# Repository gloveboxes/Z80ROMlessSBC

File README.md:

# Z80 ROMless SBC

This repository contains a work-in-progress engineering specification and
reference implementation for a ROMless Z80 computer supervised by a Raspberry
Pi Pico 2 W. The design has not yet been physically built or qualified; treat
all electrical and timing claims as proposed until the staged bench tests pass.

## Clone the project

```sh
git clone --recurse-submodules https://github.com/gloveboxes/Z80ROMlessSBC.git
```

On Windows, enable Developer Mode and run `git config --global core.symlinks true`
before cloning. Then open the `Z80ROMlessSBC` directory in a terminal or VS Code.

## Documentation

- [Browse the MkDocs source](docs/docs/en/index.md)
- [Read the published documentation](https://gloveboxes.github.io/Z80ROMlessSBC/)
- [Follow the staged breadboard implementation plan](docs/docs/en/implementation/index.md)
- [Review the KiCad schematic](hardware/kicad/exports/z80_romless_sbc.pdf)
- [Choose a PCB: DIP or partial-SMT](docs/docs/en/pcb/variants.md)

The documentation covers the component inventory, pin maps, voltage domains,
breadboard construction, Z80-assisted loading, firmware architecture, CP/M storage,
DHO814/DSLogic Plus measurements, and the complete phase-by-phase bring-up
procedure.

Phases 0-10 build the three-BB830 breadboard prototype. Two four-layer PCBs
implement the same assisted-loader circuit: an **85 x 96 mm DIP / through-hole
board** for hand assembly, and a **98.3 x 60 mm partial-SMT board** for JLCPCB
assembly. DIP is the budget-oriented option for one hand-built machine;
partial-SMT reduces hand-soldering and uses a different SRAM part.
Each PCB's 20 MHz target requires separate qualification. All builds use
fixed HCT32 logic and Z80-executed RAM loading, with no PLD programmer or
address expander.

## Related projects

Build C applications, package CP/M disks, and run them on this Z80 computer.
The supplied disks already include a default set of applications.

<table>
  <tr>
    <td width="50%" valign="top">
      <a href="https://davidly.github.io/dcc/">
        <br />
        <strong>DCC C Compiler</strong>
      </a>
      <p>Build Z80 CP/M applications on Windows, macOS, or Linux. C89 with selected C99/C11 features.</p>
      <a href="https://davidly.github.io/dcc/">Explore DCC ↗</a>
    </td>
    <td width="50%" valign="top">
      <a href="https://gloveboxes.github.io/Altair-8800-AI-Edition/">
        <br />
        <strong>Altair 8800 AI Edition</strong>
      </a>
      <p>Explore CP/M applications and build Altair disk images for deployment to this project's Pico flash storage.</p>
      <a href="https://gloveboxes.github.io/Altair-8800-AI-Edition/">Explore Altair ↗</a>
    </td>
  </tr>
</table>

See the [application and disk workflow](https://gloveboxes.github.io/Z80ROMlessSBC/related-projects/)
when you reach Phases 9–10, after completing the earlier hardware bring-up tests.

## Build

Configure and build the Pico firmware and CP/M artifacts from the repository
root:

```sh
cmake -S . -B build -G Ninja \
  -DPICO_BOARD=pico2_w
cmake --build build --target z80_cpm_images -j
```

In VS Code, open the repository folder and select **Terminal → Run Task** to
choose a build or build-and-flash task for your hardware's current phase. See
the [VS Code deployment options](docs/docs/en/system/firmware-build.md#vs-code-deployment-options)
and [toolchain setup](docs/docs/en/toolchain.md) for prerequisites and flash safety.

Phase 10 builds on the Phase 9 automatic loader.
Wi-Fi credentials and the remote-FS server address are provisioned over USB
with Ctrl-] n and stored in ENV, not compiled into firmware. The browser
terminal takes over CP/M while connected and returns it to USB on disconnect.

See [Firmware and CP/M build](docs/docs/en/system/firmware-build.md) for
prerequisites and provisioning, and [Building the documentation](docs/docs/en/development/building-docs.md)
for MkDocs and local preview commands.

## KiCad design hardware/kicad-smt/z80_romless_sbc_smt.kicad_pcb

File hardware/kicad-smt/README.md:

# Partial-SMT PCB (JLCPCB assembly variant)

This is a separate KiCad project for a 98.3 × 60 mm, four-layer board. JLCPCB
assembles every top-side SMT part, including the Raspberry Pi Pico 2 W module,
and only four parts are hand-soldered:

| Ref | Part | Assembly |
| --- | --- | --- |
| U1 | Z84C0020PEC, DIP-40 | Hand-soldered |
| A2 | 0.91 in SSD1315 OLED on a 1×4 2.54 mm female header, 5.0 mm body | Hand-soldered |
| J2 | Pico GPIO expansion header, 1×4 | Hand-soldered |
| J3 | Auxiliary external 5 V header, 1×2 | Hand-soldered |

All other parts are JLCPCB-assembled from the LCSC numbers in the schematic:

- SOIC logic and SOP-32 SRAM.
- 0603 resistors and capacitors.
- SS14 diode.
- SMT electrolytic capacitors.
- Power-only USB-C receptacle with 5.1 kΩ CC pull-downs.
- Raspberry Pi Pico 2 W (C42394205), reflowed on its castellated pads with
  KiCad's `RaspberryPi_Pico_W_SMD` footprint.

The bulk capacitors are C8-C10 = 22 µF, 35 V (LCSC C150379) and C11 = 100 µF,
16 V (LCSC C346929). Both parts use the same 6.3 × 5.4 mm case, so they look
the same size in JLCPCB's placement preview; check the BOM part numbers and
values rather than judging capacitance from the rendered body size.

## Sources

- `scripts/build-kicad-smt-schematic.py` generates the schematic, symbols and
  `reports/net_manifest.json`. Each component declares its assembly method,
  `jlc` or `hand`. JLC parts must carry an LCSC number.
- `scripts/build-kicad-smt-pcb.py` generates placement, rules, keepouts,
  labels and 3D models. `reports/z80_romless_sbc_smt.ses` holds the accepted
  Freerouting result.
- `scripts/export-jlc-assembly.py` writes the JLCPCB BOM and CPL from the
  manifest and the routed board.

## Build and validate

Save and close the project in KiCad, then run from the repository root:

```sh
PYTHON=.venv-kicad/bin/python npm run kicad:smt
```

The pipeline publishes `exports/`, `fabrication/` and `reports/` only after all
of these pass:

- ERC and netlist/manifest parity.
- PCB/DSN reproduction and zone-refilled DRC.
- Route-length budgets.
- The Gerber silk-to-mask audit (≥ 0.18 mm, target 0.20 mm).
- Every track ≥ 0.155 mm from any solder-mask opening it does not connect
  to. JLCDFM rates more than 0.15 mm as good.
- The JLC BOM/CPL consistency check.

It does not modify `hardware/kicad/`.

### JLCDFM design rules

- Solder-mask openings are 0.05 mm per side larger than the copper. J1's
  0.5 mm-pitch pads use 0.04 mm. JLCDFM flags 1:1 (zero-expansion) openings.
- J1's signal pads are trimmed 0.05 mm narrower than the stock footprint.
  This widens their copper gaps to 0.25 mm and leaves mask bridges of
  0.17 mm. JLCDFM rates bridges of 0.15 mm or more as good; the generator
  enforces 0.16 mm or a merged opening.
- After the routing session is imported, the generator straightens
  Freerouting's 45° pad exits. A run then cannot skim its own pad's mask
  opening.
- JLCDFM measures vias against rectangular pads as if the corners were
  square. A via sitting diagonally off a rounded SOIC corner therefore
  reports about 0.05 mm closer than it is. After import, the generator
  nudges each such via (and its track ends) until it is ≥ 0.16 mm from
  every square-cornered mask opening.
- The Pico footprint keeps the library's landing pads for the module's
  underside test points (TP1–TP6), SWD pads and USB shell legs. They are
  unconnected, and routed copper clears them. The library's
  "suggested RF board edge" keepouts are replaced by the enclosed antenna
  window and bridge keepout; the antenna keepout itself is retained.
- J1's stacked USB-C pad pairs (A1/B12, A4/B9, A9/B4, A12/B1) keep both
  copper pads but emit one mask and paste opening each.
- SMT pads sit at least 3.07 mm from other parts' through-hole pads.
  JLCDFM rates more than 3.05 mm as good. J2 and J3 sit 2.85 mm from the
  left edge so their pads clear the Pico castellations by 3.12 mm. J1's own shell legs are part of
  the same footprint, and JLCDFM does not report them.
- J1's plated shell slots are widened to 0.85 mm (1.9 mm and 1.75 mm long)
  with a 0.2 mm annular ring. Each slot is moved 0.125 mm outward so its
  inner edge stays at the stock position. JLCDFM rates slots wider than
  0.81 mm as good; the generator enforces 0.82 mm and at least 2:1.
  Dry-fit the purchased C393939 before ordering.

## Fabrication package

| File | Upload to |
| --- | --- |
| `fabrication/z80_romless_sbc_smt-gerbers.zip` | PCB order (Gerbers + PTH/NPTH drills) |
| `fabrication/assembly/z80_romless_sbc_smt-jlc-bom.csv` | PCBA "BOM file" |
| `fabrication/assembly/z80_romless_sbc_smt-jlc-cpl.csv` | PCBA "CPL file" |

The ZIP contains:

- Front, GND plane, +5 V plane and back copper.
- Front paste, used for the assembly stencil.
- Both solder masks and both silkscreens.
- The outline, including the enclosed Pico antenna window.
- The job file.
- Separate plated and non-plated millimetre Excellon drill files.

The full BOM (`z80_romless_sbc_smt-bom.csv`, including hand-soldered parts),
the KiCad position file, IPC-D-356 netlist, drill maps and report sit next to
the ZIP; they are not uploaded.

## JLCPCB order settings

PCB:

- FR-4, **4 layers**, 1.6 mm, 98.3 × 60 mm.
- Layer order: front, GND, +5 V, back.
- 1 oz outer and 0.5 oz inner copper.
- LeadFree HASL, green mask and white silk.
- The antenna window is an enclosed through-cutout, not a slot to the edge.
  A 4 mm FR-4 bridge keeps the top edge continuous.
- The smallest drill is the 0.4 mm via; the USB-C shell uses four 0.85 mm
  plated slots.

PCBA:

- **Top side only**.
- **Economic PCBA.** The 60 mm board height is below Standard PCBA's
  70 × 70 mm single-board minimum. Standard PCBA would require a panel with
  edge rails and fiducials.
- Upload the JLC BOM and CPL listed above. The four hand-soldered parts are
  intentionally absent from both files.
- The Pico 2 W (C42394205) is an Extended part that JLCPCB requires X-ray
  inspection for. Pre-order it into your JLCPCB parts library if it is not
  in stock.

## Before ordering

- **Check every part's rotation in JLCPCB's placement preview.** The CPL
  applies the community kicad-jlcpcb-tools correction table:
  - SOIC/SOP: +270°.
  - `CP_Elec`: 0°. The community +180° rule reversed C150379/C346929 in
    JLC's preview.
  - HRO-pattern USB-C: 0°, placed at its copper pad centre (1.5 mm inboard
    of the KiCad origin). The community +180° rule turned C393939's mouth
    inward in JLC's preview.
  - Pico 2 W module: +270°. There is no community rule for C42394205;
    JLC's preview showed its model at 0° with the USB end to the left.
  - SMA and 0603: 0°.

  Specifically confirm:
  - Pin 1 on U2, U3, U4, U7, U9 and U10.
  - The `+` lead on C8–C11.
  - The cathode band on D1, which faces Pico VSYS.
  - The USB-C mouth on J1, which faces the board edge.
  - The Pico 2 W's micro-USB connector, which faces the bottom edge, and
    its antenna over the enclosed window.
- Confirm stock for U2 (IS62C1024AL-35QLI, C397875, Extended and low stock)
  and the other Extended parts at order time.
- Confirm JLCPCB quotes J1's shell legs as part of the SMT assembly.
- Dry-fit the purchased OLED header. It must accept the module's square pins
  and fit the 1.0 mm holes.
- Physical bring-up starts at 1 MHz. Fabrication acceptance is not 20 MHz
  timing qualification.

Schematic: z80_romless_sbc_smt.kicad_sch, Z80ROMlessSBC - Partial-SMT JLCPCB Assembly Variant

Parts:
A1: Raspberry Pi Pico 2 W; RaspberryPi_Pico_W_SMD; LCSC C42394205
A2: 0.91in SSD1315 128X32 I2C OLED; OLED_SSD1315_38x12mm_Socket
C1, C2, C3, C4, C5, C6, C7: 100n; C_0603_1608Metric; LCSC C14663
C8, C9, C10: 22u; CP_Elec_6.3x5.4; LCSC C150379
C11: 100u; CP_Elec_6.3x5.4; LCSC C346929
D1: SS14; D_SMA; LCSC C2480
J1: USB-C 5V power; USB_C_Receptacle_HRO_TYPE-C-31-M-12; LCSC C393939
J2: PICO GPIO EXPANSION; PinHeader_1x04_P2.54mm_Vertical
J3: EXTERNAL 5V; PinHeader_1x02_P2.54mm_Vertical
R1, R2, R3, R4, R5, R6, R7, R8, R9, R10, R11, R12, R13, R14, R15, R16, R17, R18, R19, R20, R21, R22, R23, R24, R25, R26, R27, R28, R29, R30, R31, R32, R33, R34, R35, R36, R37, R38, R39, R40: 10k; R_0603_1608Metric; LCSC C25804
R41, R42: 5.1k; R_0603_1608Metric; LCSC C23186
U1: Z84C0020PEC; DIP-40_W15.24mm
U2: IS62C1024AL-35QLI; SOP-32_11.305x20.495mm_P1.27mm; LCSC C397875
U3: SN74HCT32DR; SOIC-14_3.9x8.7mm_P1.27mm; LCSC C6781
U4: SN74AHCT244DWR; SOIC-20W_7.5x12.8mm_P1.27mm; LCSC C2675568
U7: SN74LVC244ADWR; SOIC-20W_7.5x12.8mm_P1.27mm; LCSC C507250
U9: SN74AHCT245DWR; SOIC-20W_7.5x12.8mm_P1.27mm; LCSC C94773
U10: SN74LVC245ADWR; SOIC-20W_7.5x12.8mm_P1.27mm; LCSC C571201

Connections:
+3V3: A1.36 (3V3_OUT), A2.VCC, C5.1 (+), C7.1 (+), J2.3 (3V3_OUT), R33.2, R34.2, R35.2, R36.2, U7.20 (VCC), U10.20 (VCC)
+5V: C1.1 (+), C2.1 (+), C3.1 (+), C4.1 (+), C6.1 (+), C8.1 (+), C9.1 (+), C10.1 (+), C11.1 (+), D1.2 (A), J1.A4 (VBUS), J1.A9 (VBUS), J1.B4 (VBUS), J1.B9 (VBUS), J3.1 (+5V), R1.2, R2.2, R3.2, R4.2, R5.2, R6.2, R7.2, R8.2, R9.2, R10.2, R11.2, R12.2, R13.2, R14.2, R15.2, R16.2, R25.2, R26.2, R27.2, R28.2, R29.2, R30.2, R31.2, R32.2, U1.11 (VCC), U2.30 (CE2), U2.32 (VCC), U3.14 (VCC), U4.20 (VCC), U9.1 (DIR), U9.20 (VCC)
A0: R1.1, U1.30 (A0), U2.12 (A0), U7.11 (2A1)
A1: R2.1, U1.31 (A1), U2.11 (A1), U7.13 (2A2)
A2: R3.1, U1.32 (A2), U2.10 (A2), U7.15 (2A3)
A3: R4.1, U1.33 (A3), U2.9 (A3)
A4: R5.1, U1.34 (A4), U2.8 (A4), U7.17 (2A4)
A5: R6.1, U1.35 (A5), U2.7 (A5)
A6: R7.1, U1.36 (A6), U2.6 (A6)
A7: R8.1, U1.37 (A7), U2.5 (A7)
A8: R9.1, U1.38 (A8), U2.27 (A8)
A9: R10.1, U1.39 (A9), U2.26 (A9)
A10: R11.1, U1.40 (A10), U2.23 (A10)
A11: R12.1, U1.1 (A11), U2.25 (A11)
A12: R13.1, U1.2 (A12), U2.4 (A12)
A13: R14.1, U1.3 (A13), U2.28 (A13)
A14: R15.1, U1.4 (A14), U2.3 (A14)
A15: R16.1, U1.5 (A15), U2.31 (A15)
BOOT_READ_DISABLE: A1.7 (GP5), R34.1, U4.6 (1A3)
BOOT_READ_DISABLE_5V: U3.2 (1B), U4.14 (1Y3)
BUSACK_N: R26.1, U1.23 (BUSACK#), U7.2 (1A1)
BUSREQ_N: R25.1, U1.25 (BUSREQ#), U4.16 (1Y2)
D0: U1.14 (D0), U2.13 (D0), U9.18 (B1), U10.18 (B1)
D1: U1.15 (D1), U2.14 (D1), U9.17 (B2), U10.17 (B2)
D2: U1.12 (D2), U2.15 (D2), U9.16 (B3), U10.16 (B3)
D3: U1.8 (D3), U2.17 (D3), U9.15 (B4), U10.15 (B4)
D4: U1.7 (D4), U2.18 (D4), U9.14 (B5), U10.14 (B5)
D5: U1.9 (D5), U2.19 (D5), U9.13 (B6), U10.13 (B6)
D6: U1.10 (D6), U2.20 (D6), U9.12 (B7), U10.12 (B7)
D7: U1.13 (D7), U2.21 (D7), U9.11 (B8), U10.11 (B8)
DATA_DOWN_OE_N: A1.10 (GP7), R36.1, U10.19 (OE#)
DATA_UP_OE_N: U3.8 (3Y), U9.19 (OE#)
GND: A1.3 (GND1), A1.8 (GND2), A1.13 (GND3), A1.18 (GND4), A1.23 (GND5), A1.28 (GND6), A1.33 (AGND), A1.38 (GND7), A2.GND, C1.2 (-), C2.2 (-), C3.2 (-), C4.2 (-), C5.2 (-), C6.2 (-), C7.2 (-), C8.2 (-), C9.2 (-), C10.2 (-), C11.2 (-), J1.A1 (GND), J1.A12 (GND), J1.B1 (GND), J1.B12 (GND), J1.SH (SHIELD), J2.4 (GND), J3.2 (GND), R17.2, R18.2, R19.2, R20.2, R21.2, R22.2, R23.2, R24.2, R37.2, R38.2, R39.2, R40.2, R41.2, R42.2, U1.29 (GND), U2.16 (GND), U3.7 (GND), U3.12 (4A), U3.13 (4B), U4.1 (OE1#), U4.10 (GND), U4.15 (2A3), U4.19 (OE2#), U7.1 (1OE#), U7.10 (GND), U7.19 (2OE#), U9.10 (GND), U10.1 (DIR), U10.10 (GND)
INT_N: R31.1, U1.16 (INT#)
IORQ_N: R28.1, U1.20 (IORQ#), U3.4 (2A), U7.4 (1A2)
IO_RELEASE: A1.12 (GP9), R39.1, U3.5 (2B)
MREQ_N: R27.1, U1.19 (MREQ#), U4.8 (1A4)
NMI_N: R32.1, U1.17 (NMI#)
PICO_A0: A1.24 (GP18), U7.9 (2Y1)
PICO_A1: A1.25 (GP19), U7.7 (2Y2)
PICO_A2: A1.26 (GP20), U7.5 (2Y3)
PICO_A4: A1.27 (GP21), U7.3 (2Y4)
PICO_BUSACK_N: A1.1 (GP0), U7.18 (1Y1)
PICO_BUSREQ_N: A1.6 (GP4), R33.1, U4.4 (1A2)
PICO_CLK: A1.4 (GP2), R37.1, U4.2 (1A1)
PICO_D0: A1.14 (GP10), R17.1, U9.2 (A1), U10.2 (A1)
PICO_D1: A1.15 (GP11), R18.1, U9.3 (A2), U10.3 (A2)
PICO_D2: A1.16 (GP12), R19.1, U9.4 (A3), U10.4 (A3)
PICO_D3: A1.17 (GP13), R20.1, U9.5 (A4), U10.5 (A4)
PICO_D4: A1.19 (GP14), R21.1, U9.6 (A5), U10.6 (A5)
PICO_D5: A1.20 (GP15), R22.1, U9.7 (A6), U10.7 (A6)
PICO_D6: A1.21 (GP16), R23.1, U9.8 (A7), U10.8 (A7)
PICO_D7: A1.22 (GP17), R24.1, U9.9 (A8), U10.9 (A8)
PICO_DATA_UP_OE_N: A1.9 (GP6), R35.1, U3.10 (3B)
PICO_GP8: A1.11 (GP8), R40.1, U4.17 (2A4)
PICO_GP22: A1.29 (GP22), A2.SDA, J2.1 (GP22)
PICO_GP26: A1.31 (GP26), A2.SCK, J2.2 (GP26_ADC0)
PICO_IORQ_N: A1.2 (GP1), U7.16 (1Y2)
PICO_RD_N: A1.32 (GP27), U7.14 (1Y3)
PICO_WR_N: A1.34 (GP28), U7.12 (1Y4)
RD_5V_N: U3.1 (1A), U4.7 (2Y2)
RD_N: R29.1, U1.21 (RD#), U3.9 (3A), U4.13 (2A2), U7.6 (1A3)
RESET_N: A1.5 (GP3), R38.1, U1.26 (RESET#)
SRAM_A16: U2.2 (A16), U4.3 (2Y4)
SRAM_CE_N: U2.22 (CE#), U4.12 (1Y4)
SRAM_OE_N: U2.24 (OE#), U3.3 (1Y)
SRAM_WE_N: U2.29 (WE#), U4.9 (2Y1)
USB_CC1: J1.A5 (CC1), R41.1
USB_CC2: J1.B5 (CC2), R42.1
VSYS: A1.39 (VSYS), D1.1 (K)
WAIT_N: U1.24 (WAIT#), U3.6 (2Y)
WR_N: R30.1, U1.22 (WR#), U4.11 (2A1), U7.8 (1A4)
Z80_CLK: U1.6 (CLK), U4.18 (1Y1)

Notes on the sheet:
PORT_MONITOR
PERIPHERAL
R1-R40: discrete 10k 0603 pulls replacing the Rev B networks. R1-R16 A0-A15 to +5V; R17-R24 PICO_D0-D7 to GND; R25-R32 Z80 controls to +5V; R33-R36 3V3 startup pull-ups (breadboard R17-R20); R37-R40 startup pull-downs (breadboard R21-R24). Both data paths default disabled.
A2: socketed Stage 10 0.91in SSD1315 128x32 status OLED. Module 38.00 x 12.00 mm; 4-pin 2.54 mm header. Socket: 1x4 2.54 mm female header, 5.0 mm body (hand fit). Header order GND, VCC, SCK, SDA bottom-to-top. SDA = J2.1 / GP22; SCK = J2.2 / GP26. VCC = J2.3 / 3V3; GND = J2.4 / GND. I2C pull-ups to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
CORE
BOOT_CONTROL
PICO_DATA
Z80 is the sole SRAM address/write master. Pico injects instructions with SRAM reads inhibited. RESET_N directly joins Pico and Z80 at 3.3V.
HCT_TO_SRAM
CPU_MONITOR
DATA
BUFFERED_CONTROLS
DATA_CONTROL
HCT_TO_CPU
BANK SELECT: Pico physical pin 11 / GP8 -> U4.17. R40: 10k to GND (breadboard R24 equivalent). U4.3 -> U2.2 / A16 (5V side); LOW selects bank 0.
J2: 3.3V expansion/probe header, not a 5V input. 1: GP22/SDA; 2: GP26/SCL, shared with A2. 3: Pico 3V3 output; 4: GND. GP8 is dedicated to SRAM bank select.
MEMORY
J1: power-only USB-C receptacle (JLC C393939). VBUS -> +5V directly; no regulator, eFuse or OVP. CC1 and CC2 each 5.1k to GND (R41, R42). D+/D-/SBU unconnected; shell to GND. Use a regulated 5V USB supply only. J3 is auxiliary: only ONE supply at a time. Keep D1 to Pico VSYS; never join Pico VBUS.
PICO_TO_BUFFER
ADDRESS
CPU_TO_BUFFERS
PICO_MONITOR

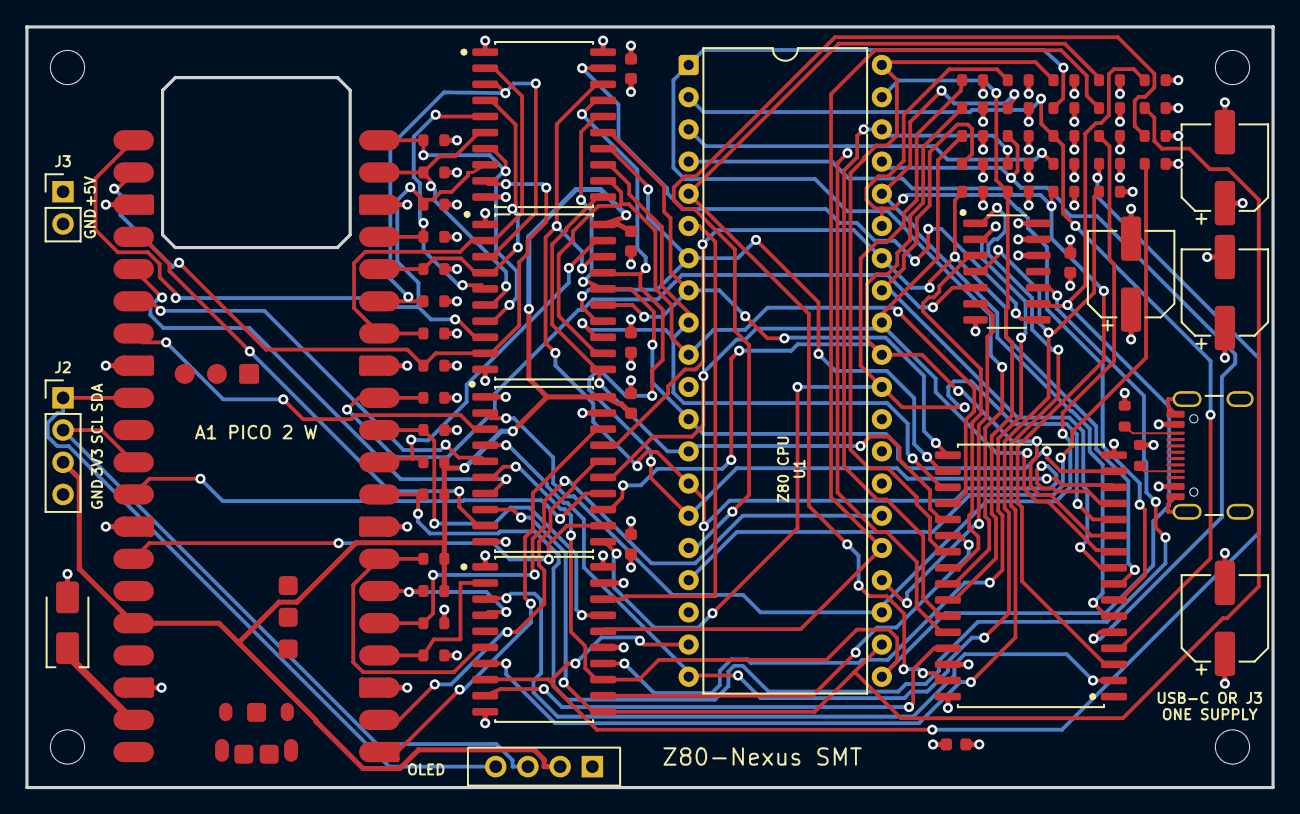
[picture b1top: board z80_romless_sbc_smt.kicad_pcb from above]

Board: 4 copper layers, 98.3 x 60.0 mm, 70 parts (0 on the bottom side), 73 nets.

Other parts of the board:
H1, H2, H3, H4: M2.5 mounting hole; MountingHole_2.7mm_M2.5

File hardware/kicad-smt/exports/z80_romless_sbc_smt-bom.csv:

"Refs","Value","Footprint","LCSC","Qty","DNP"
"A1","Raspberry Pi Pico 2 W","Module:RaspberryPi_Pico_W_SMD","C42394205","1",""
"A2","0.91in SSD1315 128X32 I2C OLED","Z80SBC:OLED_SSD1315_38x12mm_Socket","","1",""
"C1-C7","100n","Capacitor_SMD:C_0603_1608Metric","C14663","7",""
"C8-C10","22u","Capacitor_SMD:CP_Elec_6.3x5.4","C150379","3",""
"C11","100u","Capacitor_SMD:CP_Elec_6.3x5.4","C346929","1",""
"D1","SS14","Diode_SMD:D_SMA","C2480","1",""
"J1","USB-C 5V power","Connector_USB:USB_C_Receptacle_HRO_TYPE-C-31-M-12","C393939","1",""
"J2","PICO GPIO EXPANSION","Connector_PinHeader_2.54mm:PinHeader_1x04_P2.54mm_Vertical","","1",""
"J3","EXTERNAL 5V","Connector_PinHeader_2.54mm:PinHeader_1x02_P2.54mm_Vertical","","1",""
"R1-R40","10k","Resistor_SMD:R_0603_1608Metric","C25804","40",""
"R41,R42","5.1k","Resistor_SMD:R_0603_1608Metric","C23186","2",""
"U1","Z84C0020PEC","Package_DIP:DIP-40_W15.24mm","","1",""
"U2","IS62C1024AL-35QLI","Package_SO:SOP-32_11.305x20.495mm_P1.27mm","C397875","1",""
"U3","SN74HCT32DR","Package_SO:SOIC-14_3.9x8.7mm_P1.27mm","C6781","1",""
"U4","SN74AHCT244DWR","Package_SO:SOIC-20W_7.5x12.8mm_P1.27mm","C2675568","1",""
"U7","SN74LVC244ADWR","Package_SO:SOIC-20W_7.5x12.8mm_P1.27mm","C507250","1",""
"U9","SN74AHCT245DWR","Package_SO:SOIC-20W_7.5x12.8mm_P1.27mm","C94773","1",""
"U10","SN74LVC245ADWR","Package_SO:SOIC-20W_7.5x12.8mm_P1.27mm","C571201","1",""

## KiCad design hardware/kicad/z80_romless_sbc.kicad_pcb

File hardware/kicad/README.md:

# Z80 ROMless SBC KiCad sources

Revision B implements the current eight-package, Z80-assisted-loader circuit:
Pico 2 W, Z80, SRAM, HCT32, AHCT244, AHCT245, LVC245 and LVC244. SRAM A16
is driven by GP8 through U4. The design target is **20 MHz**, retaining the
project's bench-proven IC set; this PCB still requires its own qualification.

## Mechanical design

- **85 x 96 mm**, four-layer, 1.6 mm FR-4, socket-compatible through-hole parts.
  Stack-up: F.Cu signals / In1.Cu GND plane / In2.Cu +5V plane / B.Cu
  signals, written into the board file (7628 prepreg, 1.065 mm core).
- Four **2.7 mm NPTH holes for M2.5 standoffs**, one in each corner, with
  centres 4 mm from both adjacent board edges. Hole spacing is **77 x 88 mm**.
  Use standoffs/screw heads no wider than 5.4 mm overall within the
  footprint's 5.9 mm courtyard.
- Pico USB faces out of the left edge. Its antenna has a chamfered physical
  FR-4/copper cutout. Keep metal standoffs, wiring and enclosure material
  away from the antenna; mechanical clearance is not RF qualification.
- A2 reserves the complete **38 x 12 mm SSD1315 OLED** body at the upper right.
  The local footprint models the user-supplied
  [dimension drawing](https://ae-pic-a1.aliexpress-media.com/kf/Sdca8c02df9d7460298598704a34813faS.jpg):
  header centres 1.50 mm from the left edge, SDA 2.19 mm from the top, and
  2.54 mm pitch. Viewed from above, header order bottom-to-top is
  **GND, VCC, SCK, SDA**. Fit a 1x4 socket; verify its pins fit the 1.0 mm
  drills and its assembled height. Support the far end with an insulating
  spacer. No module mounting holes were dimensioned, so none are invented.
- J1 is the **onboard 21.6 x 12.7 mm USB-C power breakout** on the top
  edge, USB-C facing outward. Solder all six 2.54 mm header pins into the
  six 1.0 mm plated carrier holes. Only VBUS (+5 V) and GND are wired; CC2,
  D+, D- and CC1 have isolated pads for mechanical attachment. No module
  screw holes are used. The outline is scaled from the vendor dimension
  photo (pin row 1.36 mm from the rear edge; shell overhangs the board edge
  by about 1.5 mm), so **dry-fit the purchased module before fabrication**.
  Check USB cable access and insulate its underside; strain-relieve the
  cable.
  The 12 x 13.8 mm module description is not the selected part.
- J3 remains an optional auxiliary input/probe header:
  **pin 1 +5 V / pin 2 GND**. It shares J1's rail without source isolation:
  **connect only one supply at a time**. D1 supplies Pico VSYS; never join
  the main +5 V rail to Pico VBUS.
- J2 is the 1x4 expansion header: GP22/SDA, GP26/SCL, 3.3 V, GND. GP8 is
  dedicated to SRAM bank select and is not exposed.
  GP8 is reserved for bank select. Do not connect a second display with
  conflicting address/pull-ups while A2 is fitted.

The PCB uses **six bussed 10 kOhm arrays for all 40 pull branches**:
RN1/RN2 address pull-ups, RN3 Pico data pull-downs, RN4 control pull-ups,
RN5 four 3.3 V startup pull-ups and RN6 four startup pull-downs. RN5/RN6
replace breadboard R17-R24 electrically; the manifest records and validates
this mapping without changing the breadboard installation instructions.

## Sources and validation

- `scripts/build-kicad-schematic.py`: symbols, values, exact nets and manifest.
- `scripts/build-kicad-pcb.py`: placement, outline, cutout, pre-routes, rules,
  GND/+5V planes, stack-up and board invariants.
- `Z80SBC.pretty/` and `fp-lib-table`: project-local OLED and USB-C module
  attachment geometry.
- `reports/z80_romless_sbc.dsn`: normalized unrouted router input.
- `reports/z80_romless_sbc.ses`: authoritative accepted route.
- `reports/route-lengths.json`: measured copper, source-specific paths and
  layer changes, including actual bypass-to-supply-pin paths.

With the project closed, run from the repository root:

```sh
PYTHON=.venv-kicad/bin/python npm run kicad
```

The default is the full transactional pipeline: ERC, manifest and documented
wiring parity, exact PCB/session/DSN reproduction, DRC after zone refill,
route measurements, project-rule stability, drawings and fabrication.
Use `npm run kicad -- --schematic-only` only for schematic-only work; it does
not validate or update the PCB package.

KiCad's bundled Python is detected on macOS. Set `KICAD_PYTHON` and
`KICAD_FOOTPRINT_DIR` if needed. The schematic environment uses
`scripts/requirements-kicad.txt`; install dependencies only if missing.

## Routing with Apple container

The router-only image does not depend on Ubuntu KiCad package availability:

```sh
container build --file scripts/freerouting/Containerfile \
  --tag z80-freerouting:2.4.1 scripts/freerouting

KICAD_PYTHON=/Applications/KiCad/KiCad.app/Contents/Frameworks/Python.framework/Versions/3.9/bin/python3
"$KICAD_PYTHON" scripts/build-kicad-pcb.py

container run --rm --network none --cpus 4 --memory 6g \
  --mount "type=bind,source=$PWD/hardware/kicad/reports,target=/work" \
  z80-freerouting:2.4.1 --gui.enabled=false \
  --router.layers.routable=true,false,false,true -da \
  -de /work/z80_romless_sbc.dsn -do /work/z80_romless_sbc.ses -mp 500 -mt 1

"$KICAD_PYTHON" scripts/build-kicad-pcb.py \
  --session hardware/kicad/reports/z80_romless_sbc.ses
PYTHON=.venv-kicad/bin/python npm run kicad
```

Before routing, run placement DRC: only unconnected items may remain.
Network access is disabled during routing; `-da` also disables analytics.
The image pins Java 25 and the Freerouting 2.4.1 JAR checksum.
Only F.Cu and B.Cu route signals. In1.Cu is the GND plane and In2.Cu the
+5V plane; both are exported as DSN planes. The Z80 and Pico clocks are
locked, via-free F.Cu preroutes with 0.30 mm Clock clearance.
The router receives 0.21 mm signal clearance to provide a 0.01 mm numerical
margin over KiCad's 0.20 mm requirement, not a relaxation of the rules.

## Manufacturing and qualification

`fabrication/z80_romless_sbc-gerbers.zip` contains four copper layers,
masks, silkscreens, Edge.Cuts, job information, and PTH/NPTH drills. BOM,
placement CSV, IPC-D-356, drill maps/reports, PDF/SVG drawings and 3D preview
are adjacent outputs. Inspect the archive and confirm the fabricator's
actual stack-up and internal-cutout process before ordering.

The generator enforces silkscreen strokes of at least **0.16 mm** (JLCDFM flags exactly 0.15 mm as a warning) and
clearance of at least **0.20 mm from every drill**, including vias, and
**0.20 mm from same-side pad copper** (plus any solder-mask expansion).
Labels are positioned clear of holes and pads; straight body-outline and
polarity-hatch strokes receive small generated gaps around holes and pads
without changing copper or removing polarity marks.
The full pipeline checks these dimensions as well as KiCad ERC/DRC.
Run `scripts/test_kicad_silkscreen.py` with KiCad's bundled Python for the
focused geometry regression tests. Re-run the manufacturer's DFM check on
each new upload; local checks are not a substitute for its production review.

Both clock paths are via-free. Current paths are 49.56 mm Pico-to-U4 and
62.16 mm U4-to-Z80. Bus matching is assessed by source/receiver path, not
total tree copper. See the [design review](../../docs/docs/en/pcb/design-considerations.md)
for measurements and the long raw-RD path requiring receive-pin timing review.

Zero ERC/DRC and exact regeneration do not qualify physical operation.
Start PCB bring-up at 1 MHz, then qualify up to 20 MHz using SRAM patterns,
bank switching, repeated boots, CP/M/I/O soak and receive-pin measurements.
Do not treat one 50 ns clock period as the complete Z80 memory-access window.

Apply J1 power (or J3 power, not both) before connecting Pico USB; disconnect
Pico USB before removing main power. Pico-USB-only operation of the populated
AHCT245 circuit is unsupported.
Inspect actual socket envelopes, OLED height, screw-head clearance and
electrolytic/diode polarity; the render lacks socket, OLED, USB-C breakout
and standoff models.

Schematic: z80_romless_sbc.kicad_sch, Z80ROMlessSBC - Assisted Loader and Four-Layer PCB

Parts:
A1: Raspberry Pi Pico 2 W; RaspberryPi_Pico_Common_THT
A2: 0.91in SSD1315 128X32 I2C OLED; OLED_SSD1315_38x12mm_Socket
C1, C2, C3, C4, C5, C6, C7: 100n; C_Disc_D5.0mm_W2.5mm_P2.50mm
C8, C9, C10: 22u; CP_Radial_D4.0mm_P2.00mm
C11: 100u; CP_Radial_D6.3mm_P2.50mm
D1: 1N5819; D_DO-41_SOD81_P10.16mm_Horizontal
J1: USB-C 5V POWER BREAKOUT; USB_C_Breakout_6Pin_P2.54mm_Solder
J2: PICO GPIO EXPANSION; PinHeader_1x04_P2.54mm_Vertical
J3: EXTERNAL 5V; PinHeader_1x02_P2.54mm_Vertical
RN1, RN2, RN3, RN4: 8x10k bussed; R_Array_SIP9
RN5, RN6: 4x10k bussed; R_Array_SIP5
U1: Z84C0020PEC; DIP-40_W15.24mm
U2: AS6C1008-55PCN; DIP-32_W15.24mm
U3: SN74HCT32N; DIP-14_W7.62mm
U4: SN74AHCT244N; DIP-20_W7.62mm
U7: SN74LVC244AN; DIP-20_W7.62mm
U9: SN74AHCT245N Pico-to-bus; DIP-20_W7.62mm
U10: SN74LVC245AN bus-to-Pico; DIP-20_W7.62mm

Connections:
+3V3: A1.36 (3V3_OUT), A2.VCC, C5.1 (+), C7.1 (+), J2.3 (3V3_OUT), RN5.1 (COMMON), U7.20 (VCC), U10.20 (VCC)
+5V: C1.1 (+), C2.1 (+), C3.1 (+), C4.1 (+), C6.1 (+), C8.1 (+), C9.1 (+), C10.1 (+), C11.1 (+), D1.2 (A), J1.VBUS, J3.1 (+5V), RN1.1 (COMMON), RN2.1 (COMMON), RN4.1 (COMMON), U1.11 (VCC), U2.30 (CE2), U2.32 (VCC), U3.14 (VCC), U4.20 (VCC), U9.1 (DIR), U9.20 (VCC)
A0: RN1.2 (R1), U1.30 (A0), U2.12 (A0), U7.11 (2A1)
A1: RN1.3 (R2), U1.31 (A1), U2.11 (A1), U7.13 (2A2)
A2: RN1.4 (R3), U1.32 (A2), U2.10 (A2), U7.15 (2A3)
A3: RN1.5 (R4), U1.33 (A3), U2.9 (A3)
A4: RN1.6 (R5), U1.34 (A4), U2.8 (A4), U7.17 (2A4)
A5: RN1.7 (R6), U1.35 (A5), U2.7 (A5)
A6: RN1.8 (R7), U1.36 (A6), U2.6 (A6)
A7: RN1.9 (R8), U1.37 (A7), U2.5 (A7)
A8: RN2.2 (R1), U1.38 (A8), U2.27 (A8)
A9: RN2.3 (R2), U1.39 (A9), U2.26 (A9)
A10: RN2.4 (R3), U1.40 (A10), U2.23 (A10)
A11: RN2.5 (R4), U1.1 (A11), U2.25 (A11)
A12: RN2.6 (R5), U1.2 (A12), U2.4 (A12)
A13: RN2.7 (R6), U1.3 (A13), U2.28 (A13)
A14: RN2.8 (R7), U1.4 (A14), U2.3 (A14)
A15: RN2.9 (R8), U1.5 (A15), U2.31 (A15)
BOOT_READ_DISABLE: A1.7 (GP5), RN5.3 (R2), U4.6 (1A3)
BOOT_READ_DISABLE_5V: U3.2 (1B), U4.14 (1Y3)
BUSACK_N: RN4.3 (R2), U1.23 (BUSACK#), U7.2 (1A1)
BUSREQ_N: RN4.2 (R1), U1.25 (BUSREQ#), U4.16 (1Y2)
D0: U1.14 (D0), U2.13 (D0), U9.18 (B1), U10.18 (B1)
D1: U1.15 (D1), U2.14 (D1), U9.17 (B2), U10.17 (B2)
D2: U1.12 (D2), U2.15 (D2), U9.16 (B3), U10.16 (B3)
D3: U1.8 (D3), U2.17 (D3), U9.15 (B4), U10.15 (B4)
D4: U1.7 (D4), U2.18 (D4), U9.14 (B5), U10.14 (B5)
D5: U1.9 (D5), U2.19 (D5), U9.13 (B6), U10.13 (B6)
D6: U1.10 (D6), U2.20 (D6), U9.12 (B7), U10.12 (B7)
D7: U1.13 (D7), U2.21 (D7), U9.11 (B8), U10.11 (B8)
DATA_DOWN_OE_N: A1.10 (GP7), RN5.5 (R4), U10.19 (OE#)
DATA_UP_OE_N: U3.8 (3Y), U9.19 (OE#)
GND: A1.3 (GND1), A1.8 (GND2), A1.13 (GND3), A1.18 (GND4), A1.23 (GND5), A1.28 (GND6), A1.33 (AGND), A1.38 (GND7), A2.GND, C1.2 (-), C2.2 (-), C3.2 (-), C4.2 (-), C5.2 (-), C6.2 (-), C7.2 (-), C8.2 (-), C9.2 (-), C10.2 (-), C11.2 (-), J1.GND, J2.4 (GND), J3.2 (GND), RN3.1 (COMMON), RN6.1 (COMMON), U1.29 (GND), U2.16 (GND), U3.7 (GND), U3.12 (4A), U3.13 (4B), U4.1 (OE1#), U4.10 (GND), U4.15 (2A3), U4.19 (OE2#), U7.1 (1OE#), U7.10 (GND), U7.19 (2OE#), U9.10 (GND), U10.1 (DIR), U10.10 (GND)
INT_N: RN4.8 (R7), U1.16 (INT#)
IORQ_N: RN4.5 (R4), U1.20 (IORQ#), U3.4 (2A), U7.4 (1A2)
IO_RELEASE: A1.12 (GP9), RN6.4 (R3), U3.5 (2B)
MREQ_N: RN4.4 (R3), U1.19 (MREQ#), U4.8 (1A4)
NMI_N: RN4.9 (R8), U1.17 (NMI#)
PICO_A0: A1.24 (GP18), U7.9 (2Y1)
PICO_A1: A1.25 (GP19), U7.7 (2Y2)
PICO_A2: A1.26 (GP20), U7.5 (2Y3)
PICO_A4: A1.27 (GP21), U7.3 (2Y4)
PICO_BUSACK_N: A1.1 (GP0), U7.18 (1Y1)
PICO_BUSREQ_N: A1.6 (GP4), RN5.2 (R1), U4.4 (1A2)
PICO_CLK: A1.4 (GP2), RN6.2 (R1), U4.2 (1A1)
PICO_D0: A1.14 (GP10), RN3.2 (R1), U9.2 (A1), U10.2 (A1)
PICO_D1: A1.15 (GP11), RN3.3 (R2), U9.3 (A2), U10.3 (A2)
PICO_D2: A1.16 (GP12), RN3.4 (R3), U9.4 (A3), U10.4 (A3)
PICO_D3: A1.17 (GP13), RN3.5 (R4), U9.5 (A4), U10.5 (A4)
PICO_D4: A1.19 (GP14), RN3.6 (R5), U9.6 (A5), U10.6 (A5)
PICO_D5: A1.20 (GP15), RN3.7 (R6), U9.7 (A6), U10.7 (A6)
PICO_D6: A1.21 (GP16), RN3.8 (R7), U9.8 (A7), U10.8 (A7)
PICO_D7: A1.22 (GP17), RN3.9 (R8), U9.9 (A8), U10.9 (A8)
PICO_DATA_UP_OE_N: A1.9 (GP6), RN5.4 (R3), U3.10 (3B)
PICO_GP8: A1.11 (GP8), RN6.5 (R4), U4.17 (2A4)
PICO_GP22: A1.29 (GP22), A2.SDA, J2.1 (GP22)
PICO_GP26: A1.31 (GP26), A2.SCK, J2.2 (GP26_ADC0)
PICO_IORQ_N: A1.2 (GP1), U7.16 (1Y2)
PICO_RD_N: A1.32 (GP27), U7.14 (1Y3)
PICO_WR_N: A1.34 (GP28), U7.12 (1Y4)
RD_5V_N: U3.1 (1A), U4.7 (2Y2)
RD_N: RN4.6 (R5), U1.21 (RD#), U3.9 (3A), U4.13 (2A2), U7.6 (1A3)
RESET_N: A1.5 (GP3), RN6.3 (R2), U1.26 (RESET#)
SRAM_A16: U2.2 (A16), U4.3 (2Y4)
SRAM_CE_N: U2.22 (CE#), U4.12 (1Y4)
SRAM_OE_N: U2.24 (OE#), U3.3 (1Y)
SRAM_WE_N: U2.29 (WE#), U4.9 (2Y1)
VSYS: A1.39 (VSYS), D1.1 (K)
WAIT_N: U1.24 (WAIT#), U3.6 (2Y)
WR_N: RN4.7 (R6), U1.22 (WR#), U4.11 (2A1), U7.8 (1A4)
Z80_CLK: U1.6 (CLK), U4.18 (1Y1)

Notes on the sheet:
MEMORY BOARD
PERIPHERAL BOARD
HCT_TO_CPU
BANK SELECT: Pico physical pin 11 / GP8 -> U4.17. RN6.5: 10k to RN6.1 / GND (breadboard R24 equivalent). U4.3 -> U2.2 / A16 (5V side); LOW selects bank 0.
CPU_TO_BUFFERS
PICO_MONITOR
J1: onboard USB-C 5V breakout, not a regulator. 21.6 x 12.7 mm body; photo-scaled outline, dry-fit first. Solder ALL six 2.54mm pins into 1.0mm carrier holes. Photo pad order: CC2, D+, D-, CC1, GND, VBUS. Only VBUS -> +5V and GND wired; other pads isolated. No module screw holes; insulate/support u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
PORT_MONITOR
DATA_CONTROL
Z80 is the sole SRAM address/write master. Pico injects instructions with SRAM reads inhibited. RESET_N directly joins Pico and Z80 at 3.3V.
PICO_TO_BUFFER
HCT_TO_SRAM
DATA
ADDRESS
CORE BOARD
BUFFERED_CONTROLS
J2: 3.3V expansion/probe header, not a 5V input. 1: GP22/SDA; 2: GP26/SCL, shared with A2. 3: Pico 3V3 output; 4: GND. GP8 is dedicated to SRAM bank select.
CPU_MONITOR
PICO_DATA
BOOT_CONTROL
RN1-RN4: address, data and control bias. RN5: four 3V3 startup pull-ups (breadboard R17-R20). RN6: four startup pull-downs (breadboard R21-R24). Both data paths default disabled.
A2: socketed Stage 10 0.91in SSD1315 128x32 status OLED. Module 38.00 x 12.00 mm; 4-pin 2.54 mm header. Header centres 1.50mm from left; SDA 2.19mm from top. Header order GND, VCC, SCK, SDA bottom-to-top. SDA = J2.1 / GP22; SCK = J2.2 / GP26. VCC = J2.3 / 3V3; GND = J2.4 / GND. I2C pull-ups to 3.3V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

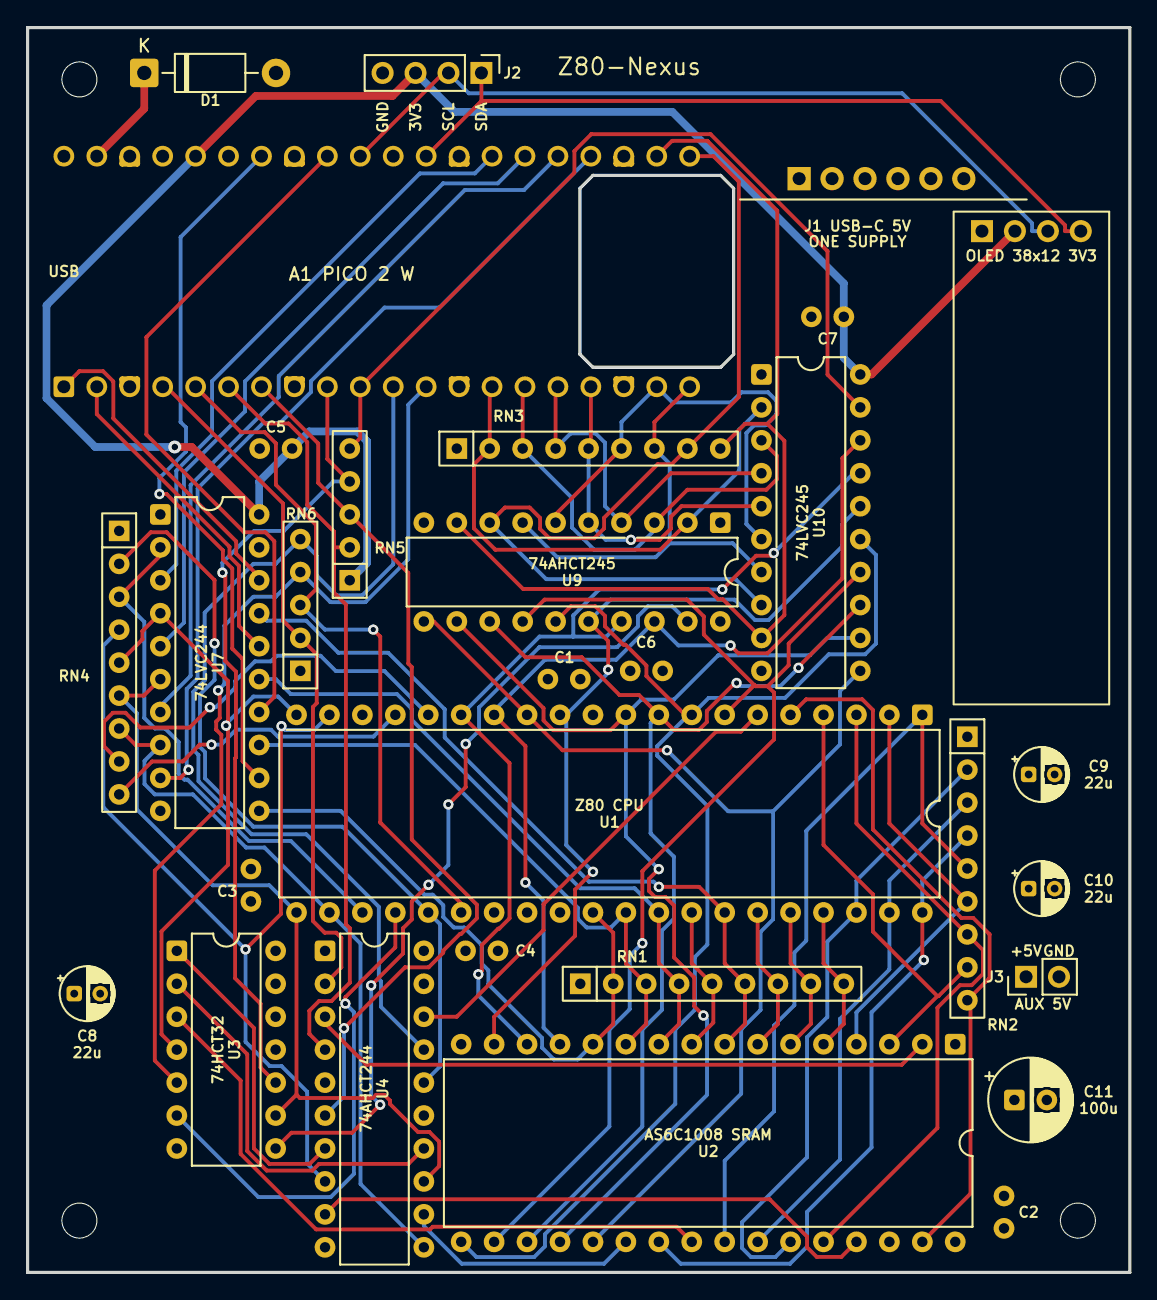
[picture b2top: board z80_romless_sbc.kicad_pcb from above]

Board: 4 copper layers, 85.0 x 96.0 mm, 34 parts (0 on the bottom side), 71 nets.

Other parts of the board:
H1, H2, H3, H4: M2.5 mounting hole; MountingHole_2.7mm_M2.5

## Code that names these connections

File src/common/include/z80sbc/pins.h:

#ifndef Z80SBC_PINS_H
#define Z80SBC_PINS_H

enum {
  PIN_BUSACK_N = 0,
  PIN_IORQ_N = 1,
  PIN_CLK = 2,
  PIN_RESET_N = 3,
  PIN_BUSREQ_N = 4,
  PIN_BOOT_READ_DISABLE = 5,
  PIN_DATA_UP_OE_N = 6,
  PIN_DATA_DOWN_OE_N = 7,
  PIN_MEMORY_BANK = 8,
  PIN_IO_RELEASE = 9,
  PIN_DATA_0 = 10,
  PIN_DATA_1 = 11,
  PIN_DATA_2 = 12,
  PIN_DATA_3 = 13,
  PIN_DATA_4 = 14,
  PIN_DATA_5 = 15,
  PIN_DATA_6 = 16,
  PIN_DATA_7 = 17,
  PIN_PORT_A0 = 18,
  PIN_PORT_A1 = 19,
  PIN_PORT_A2 = 20,
  PIN_PORT_A4 = 21,
  PIN_RD_N = 27,
  PIN_WR_N = 28,
};

#endif
